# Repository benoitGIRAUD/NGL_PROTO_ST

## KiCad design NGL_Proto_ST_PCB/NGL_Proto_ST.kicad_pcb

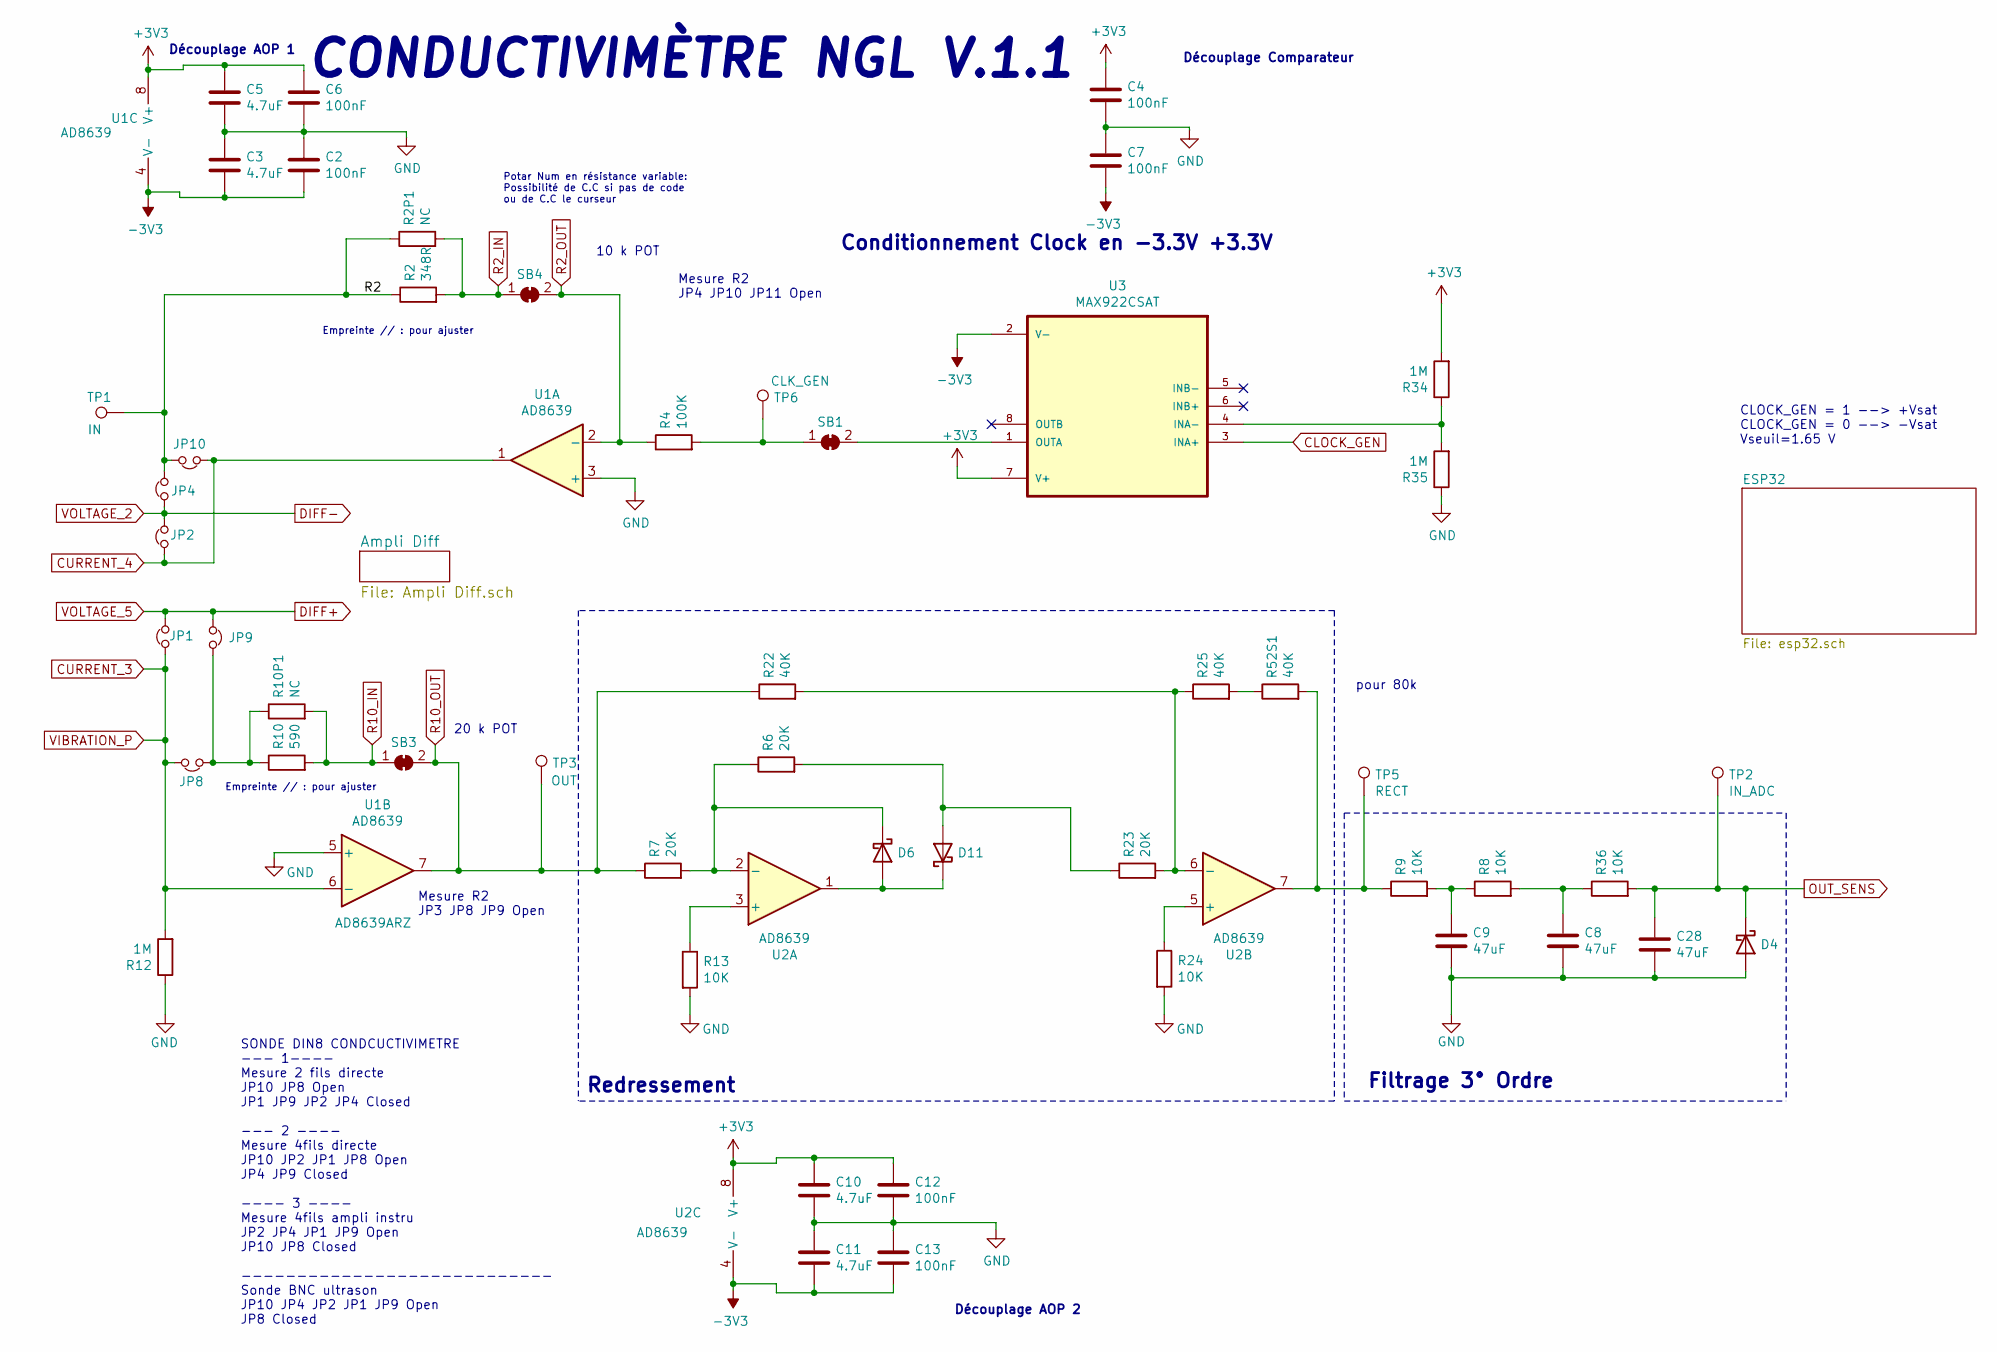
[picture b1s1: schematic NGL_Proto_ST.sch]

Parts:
C2, C4, C6, C7, C12, C13: 100nF; C_0805_2012Metric_Pad1.18x1.45mm_HandSolder
C3, C5, C10, C11: 4.7uF; C_0805_2012Metric_Pad1.18x1.45mm_HandSolder
C8, C9, C28: 47uF; C_0805_2012Metric_Pad1.18x1.45mm_HandSolder
D4, D6, D11: D_Schottky; SOT-323_SC-70_Handsoldering; MPN BAT54WFILMY
JP1, JP2, JP4, JP8, JP9, JP10: Jumper_NC_Small; PinHeader_1x02_P2.54mm_Vertical
R2: 348R; R_0805_2012Metric_Pad1.20x1.40mm_HandSolder
R2P1, R10P1: NC; R_0805_2012Metric_Pad1.20x1.40mm_HandSolder
R4: 100K; R_0805_2012Metric_Pad1.20x1.40mm_HandSolder
R6, R7, R23: 20K; R_0805_2012Metric_Pad1.20x1.40mm_HandSolder
R8, R9, R13, R24, R36: 10K; R_0805_2012Metric_Pad1.20x1.40mm_HandSolder
R10: 590; R_0805_2012Metric_Pad1.20x1.40mm_HandSolder
R12, R34, R35: 1M; R_0805_2012Metric_Pad1.20x1.40mm_HandSolder
R22, R25, R52S1: 40K; R_0805_2012Metric_Pad1.20x1.40mm_HandSolder
SB1, SB3, SB4: SB; SolderJumper-2_P1.3mm_Open_RoundedPad1.0x1.5mm
TP1: IN; PinHeader_1x01_P2.54mm_Vertical
TP2: IN_ADC; PinHeader_1x01_P2.54mm_Vertical
TP3: OUT; PinHeader_1x01_P2.54mm_Vertical
TP5: RECT; PinHeader_1x01_P2.54mm_Vertical
TP6: CLK_GEN; TestPoint_Pad_D3.0mm
U1, U2: AD8639; ADA4522-2ARZ; MPN AD8639
U3: MAX922CSAT; SOIC127P600X175-8N; MPN MAX922CSAT

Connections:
-3V3: C2.2, C3.2, C7.2, C11.2, C13.2, U1.4 (V-), U2.4 (V-), U3.2 (V-); also elsewhere on the board
/R2: JP4.2, JP10.2, R2.1, R2P1.1, TP1.1
CLOCK_GEN: U3.3 (INA+); also elsewhere on the board
CURRENT_3: JP1.1, JP8.2, R12.2, U1.6 (-); also elsewhere on the board
CURRENT_4: JP2.1, JP10.1, U1.1; also elsewhere on the board
DIFF+: JP1.2, JP9.1; also elsewhere on the board
DIFF-: JP2.2, JP4.1; also elsewhere on the board
unnamed: C8.1, R8.2, R36.1
unnamed: C9.1, R8.1, R9.2
unnamed: D6.1 (K), R6.1, R7.2, U2.2 (-)
unnamed: D6.2 (A), D11.1 (K), U2.1
unnamed: D11.2 (A), R6.2, R23.1
unnamed: JP8.1, JP9.2, R10.1, R10P1.1
unnamed: R4.2, SB1.1 (A), TP6.1
unnamed: R13.1, U2.3 (+)
unnamed: R22.2, R23.2, R25.1, U2.6 (-)
unnamed: R24.1, U2.5 (+)
unnamed: R25.2, R52S1.1
unnamed: R34.1, R35.2, U3.4 (INA-)
unnamed: R9.1, R52S1.2, TP5.1, U2.7
unnamed: SB1.2 (B), U3.1 (OUTA)
OUT_SENS: C28.1, D4.1 (K), R36.2, TP2.1; also elsewhere on the board
R2_IN: R2.2, R2P1.2, SB4.1 (A); also elsewhere on the board
R2_OUT: R4.1, SB4.2 (B), U1.2 (-); also elsewhere on the board
R10_IN: R10.2, R10P1.2, SB3.1 (A); also elsewhere on the board
R10_OUT: R7.1, R22.1, SB3.2 (B), TP3.1, U1.7; also elsewhere on the board

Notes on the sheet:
SONDE DIN8 CONDCUCTIVIMETRE --- 1---- Mesure 2 fils directe JP10 JP8 Open JP1 JP9 JP2 JP4 Closed --- 2 ---- Mesure 4fils directe JP10 JP2 JP1 JP8 Open JP4 JP9 Closed ---- 3 ---- Mesure 4fils ampli instru JP2 JP4 JP1 JP9 Open JP10 JP8 Closed ---------------------------- Sonde BNC ultrason JP10 JP4 J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
Mesure R2 JP4 JP10 JP11 Open
Mesure R2 JP3 JP8 JP9 Open
Découplage AOP 2
Découplage AOP 1
Conditionnement Clock en -3.3V +3.3V
Redressement
Filtrage 3° Ordre
Découplage Comparateur
CLOCK_GEN = 1 --> +Vsat CLOCK_GEN = 0 --> -Vsat Vseuil=1.65 V
Potar Num en résistance variable: Possibilité de C.C si pas de code ou de C.C le curseur
pour 80k
CONDUCTIVIMÈTRE NGL V.1.1
10 k POT
20 k POT
Empreinte // : pour ajuster

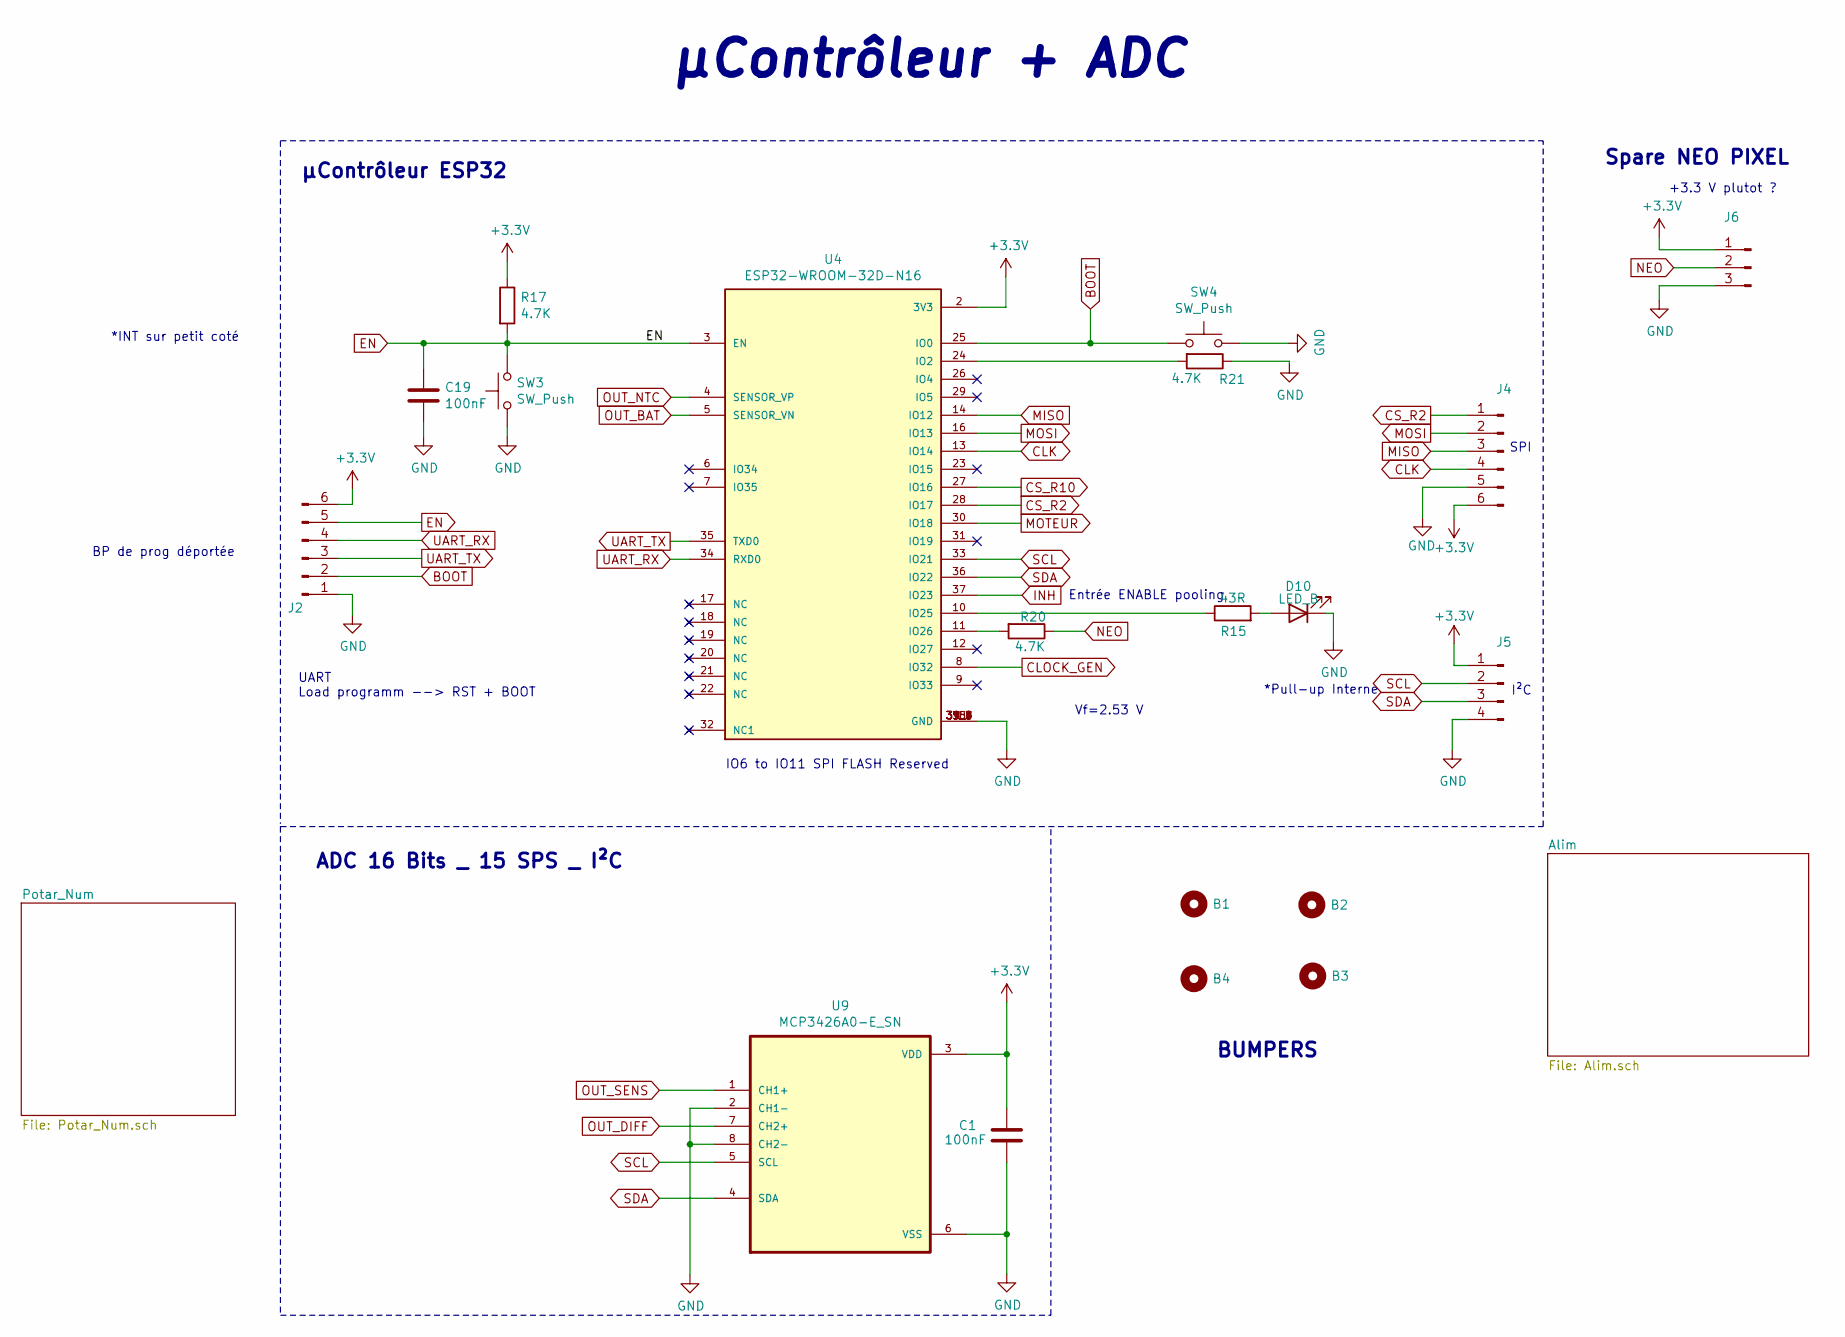
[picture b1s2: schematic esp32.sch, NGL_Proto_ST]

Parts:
B1, B2, B3, B4: BUMPER; SJ5003; MPN SJ5003
C1, C19: 100nF; C_0805_2012Metric_Pad1.18x1.45mm_HandSolder
D10: LED_B; LED_D3.0mm
J2: Conn_01x04_Male; PinHeader_1x06_P2.54mm_Vertical
J4: Conn_01x06_Male; PinHeader_1x06_P2.54mm_Vertical
J5: Conn_01x04_Male; PinHeader_1x04_P2.54mm_Vertical
J6: Conn_01x03_Male; PinHeader_1x03_P2.54mm_Vertical
R15: 43R; R_0805_2012Metric_Pad1.20x1.40mm_HandSolder
R17, R20, R21: 4.7K; R_0805_2012Metric_Pad1.20x1.40mm_HandSolder
SW3, SW4: SW_Push; 3-1825910-5; MPN 3-1825910-5
U4: ESP32-WROOM-32D-N16; MODULE_ESP32-WROOM-32D; PARTREV 1.4
U9: MCP3426A0-E_SN; SOIC127P600X175-8N; MPN MCP3426A0-E_SN

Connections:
BOOT: J2.2, SW4.1, U4.25 (IO0)
CLK: J4.4, U4.13 (IO14); also elsewhere on the board
CLOCK_GEN: U4.8 (IO32); also elsewhere on the board
CS_R10: U4.27 (IO16); also elsewhere on the board
EN: C19.1, J2.5, R17.2, SW3.2, U4.3 (EN)
INH: U4.37 (IO23); also elsewhere on the board
MISO: J4.3, U4.14 (IO12)
MOSI: J4.2, U4.16 (IO13); also elsewhere on the board
MOTEUR: U4.30 (IO18); also elsewhere on the board
NEO: J6.2, R20.1
unnamed: D10.2 (A), R15.2
unnamed: R15.1, U4.10 (IO25)
unnamed: R20.2, U4.11 (IO26)
unnamed: R21.2, U4.24 (IO2)
OUT_BAT: U4.5 (SENSOR_VN); also elsewhere on the board
OUT_DIFF: U9.7 (CH2+); also elsewhere on the board
OUT_NTC: U4.4 (SENSOR_VP); also elsewhere on the board
OUT_SENS: U9.1 (CH1+); also elsewhere on the board
SCL: J5.2, U4.33 (IO21), U9.5 (SCL)
SDA: J5.3, U4.36 (IO22), U9.4 (SDA)

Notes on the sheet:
IO6 to IO11 SPI FLASH Reserved
UART Load programm --> RST + BOOT
SPI
I²C
μContrôleur ESP32
Spare NEO PIXEL
ADC 16 Bits _ 15 SPS _ I²C
BUMPERS
+3.3 V plutot ?
Vf=2.53 V
μContrôleur + ADC
*Pull-up Interne
*INT sur petit coté
Entrée ENABLE pooling
BP de prog déportée

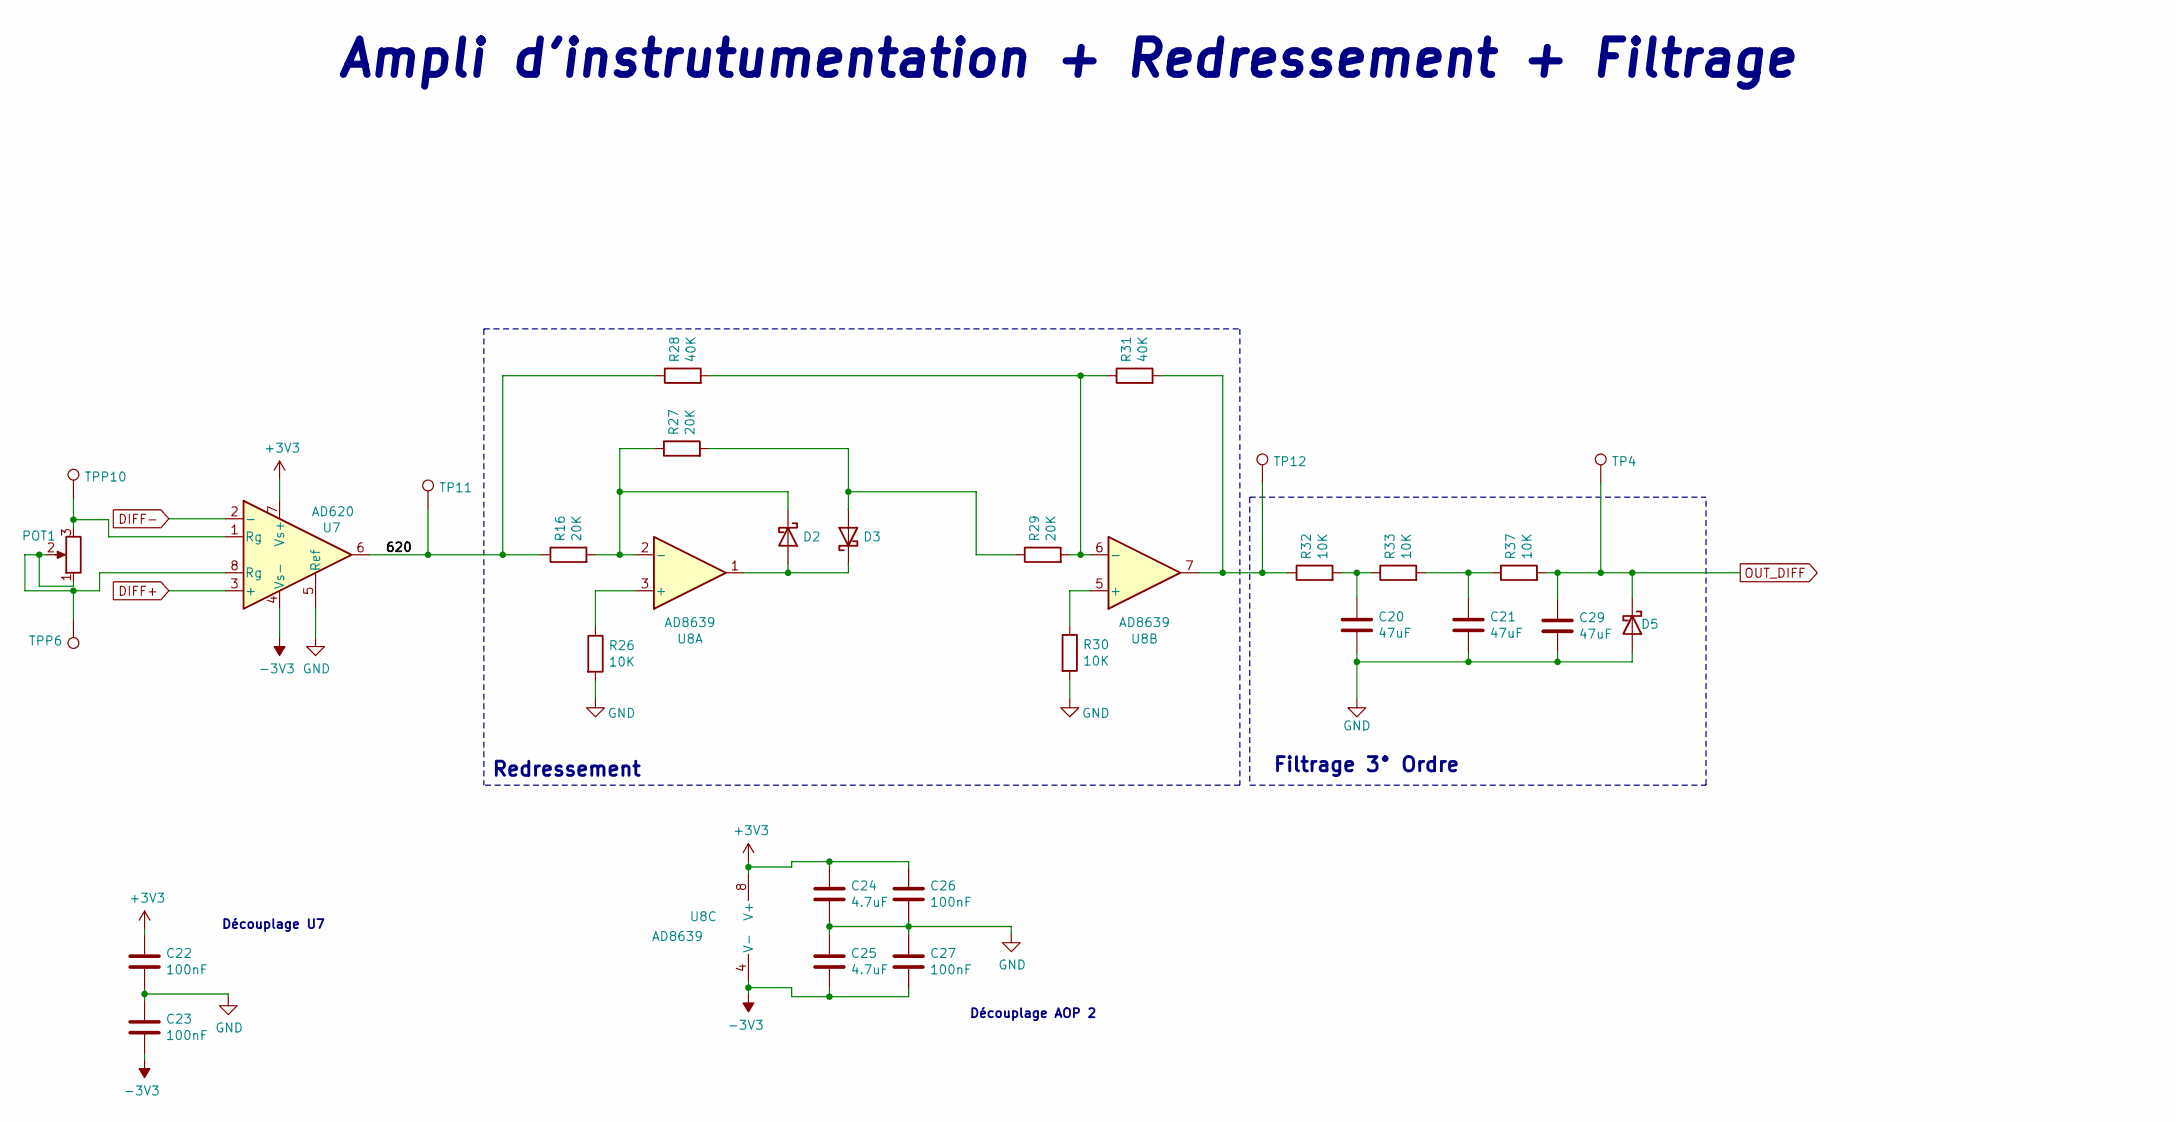
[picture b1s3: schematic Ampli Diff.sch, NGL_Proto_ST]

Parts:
C20, C21, C29: 47uF; C_0805_2012Metric_Pad1.18x1.45mm_HandSolder
C22, C23, C26, C27: 100nF; C_0805_2012Metric_Pad1.18x1.45mm_HandSolder
C24, C25: 4.7uF; C_0805_2012Metric_Pad1.18x1.45mm_HandSolder
D2, D3, D5: D_Schottky; SOT-323_SC-70_Handsoldering; MPN BAT54WFILMY
POT1: 50k; 3224X-1-502E
R16, R27, R29: 20K; R_0805_2012Metric_Pad1.20x1.40mm_HandSolder
R26, R30, R32, R33, R37: 10K; R_0805_2012Metric_Pad1.20x1.40mm_HandSolder
R28, R31: 40K; R_0805_2012Metric_Pad1.20x1.40mm_HandSolder
TP4, TP11, TP12: TestPoint; PinHeader_1x01_P2.54mm_Vertical
TPP6: TestPoint; TestPoint_Pad_D3.0mm
TPP10: TestPointPad; TestPoint_Pad_D3.0mm
U7: AD620; SOIC127P600X175-8N; MPN AD620
U8: AD8639; ADA4522-2ARZ; MPN AD8639

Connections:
-3V3: C23.2, C25.2, C27.2, U7.4 (Vs-), U8.4 (V-); also elsewhere on the board
/Ampli Diff/620: R16.1, R28.1, TP11.1, U7.6
DIFF+: U7.3 (+); also elsewhere on the board
DIFF-: U7.2 (-); also elsewhere on the board
unnamed: C20.1, R32.2, R33.1
unnamed: C21.1, R33.2, R37.1
unnamed: D2.1 (K), R16.2, R27.1, U8.2 (-)
unnamed: D2.2 (A), D3.1 (K), U8.1
unnamed: D3.2 (A), R27.2, R29.1
unnamed: POT1.1, POT1.2, TPP6.1, U7.8 (Rg)
unnamed: POT1.3, TPP10.1, U7.1 (Rg)
unnamed: R26.1, U8.3 (+)
unnamed: R28.2, R29.2, R31.1, U8.6 (-)
unnamed: R30.1, U8.5 (+)
unnamed: R31.2, R32.1, TP12.1, U8.7
OUT_DIFF: C29.1, D5.1 (K), R37.2, TP4.1; also elsewhere on the board

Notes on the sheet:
Redressement
Filtrage 3° Ordre
Ampli d'instrutumentation + Redressement + Filtrage
Découplage U7
Découplage AOP 2

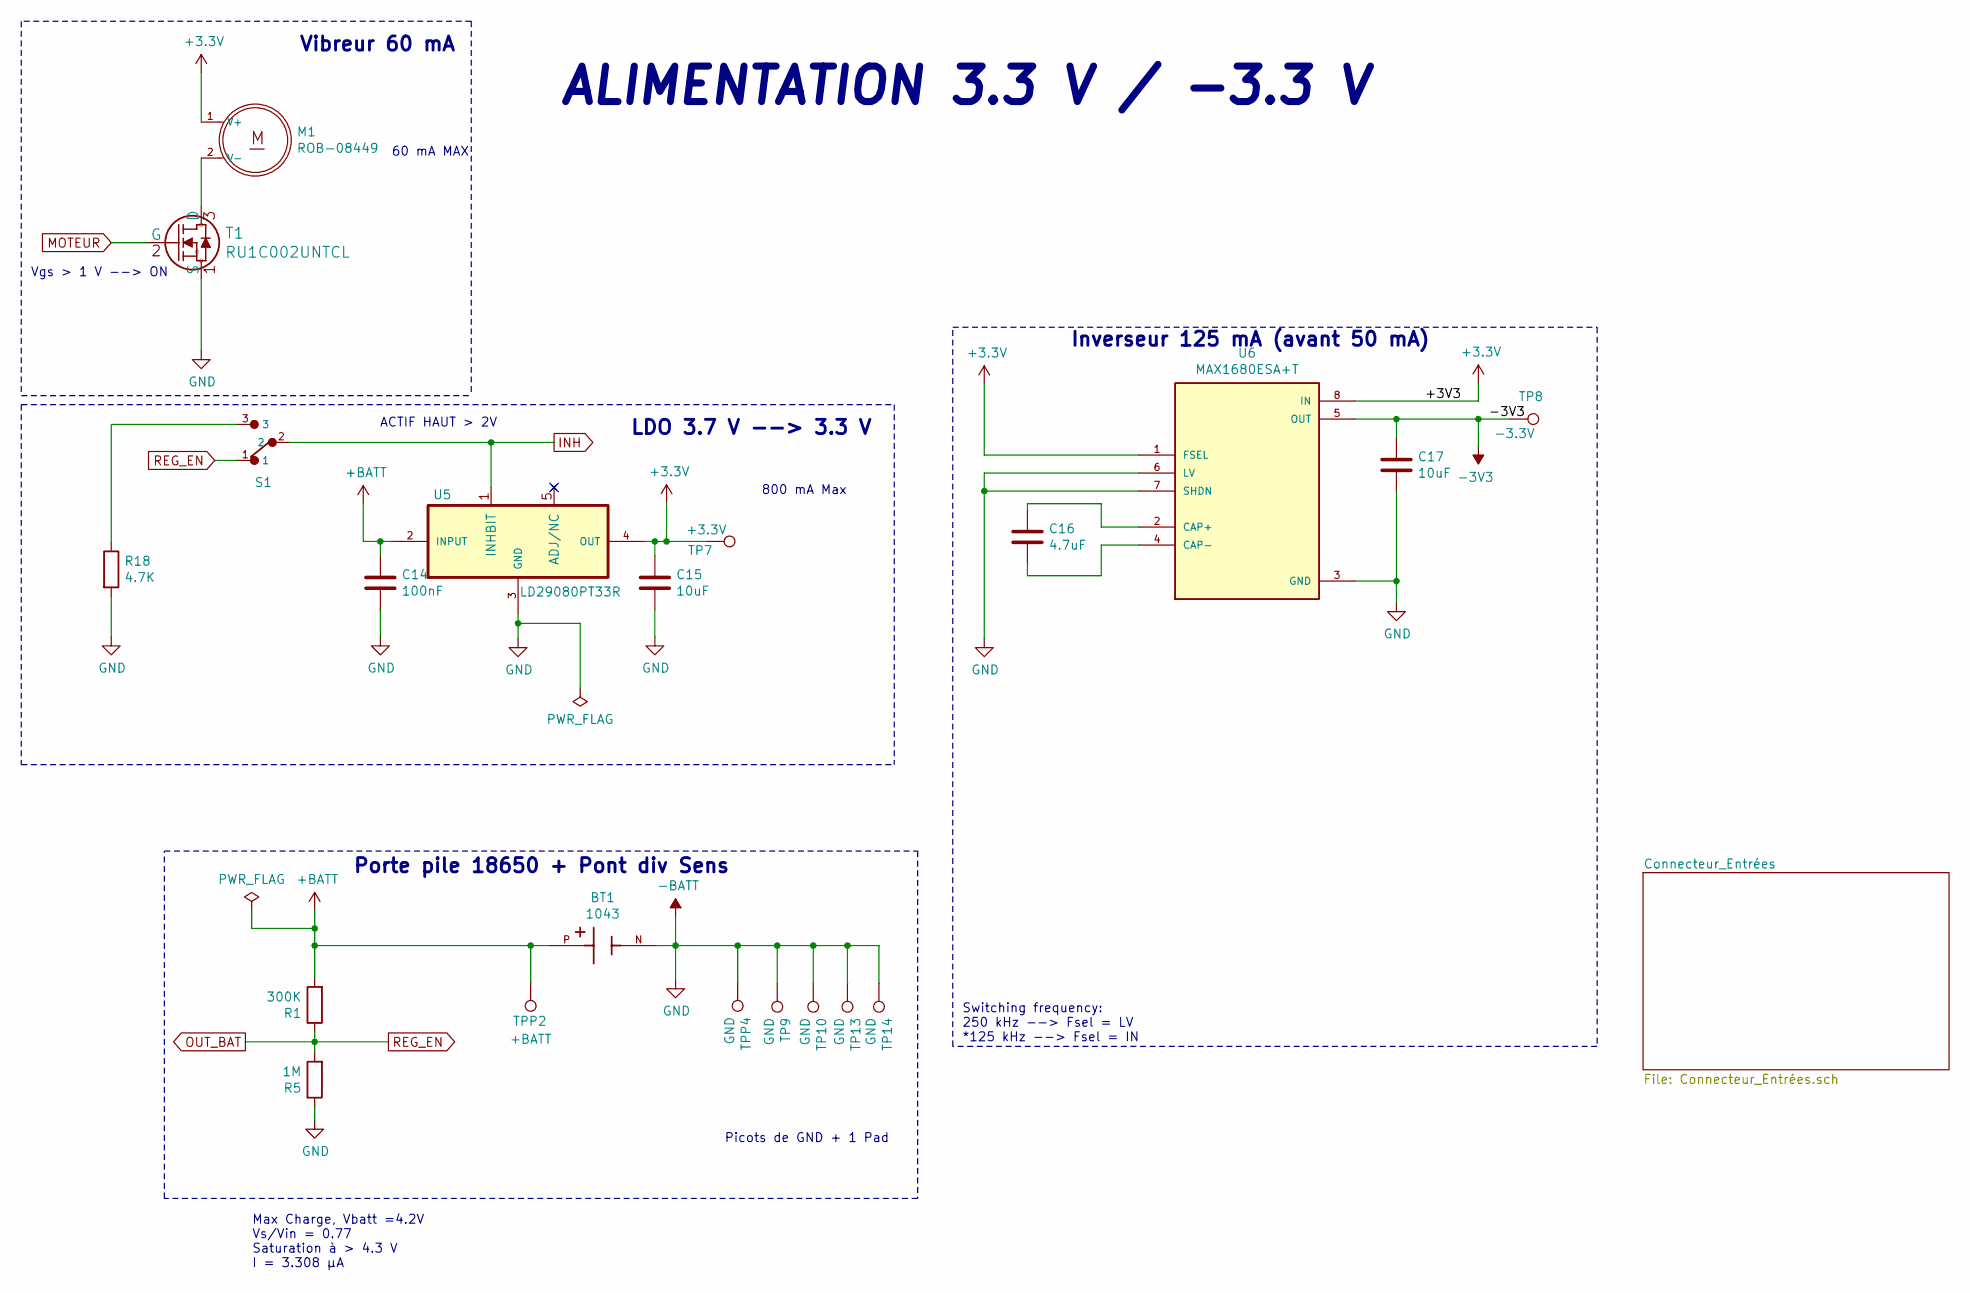
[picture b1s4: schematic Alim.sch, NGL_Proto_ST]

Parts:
BT1: 1043; BAT_1043; MPN 1043
C14: 100nF; C_0805_2012Metric_Pad1.18x1.45mm_HandSolder
C15, C17: 10uF; C_0805_2012Metric_Pad1.18x1.45mm_HandSolder
C16: 4.7uF; C_0805_2012Metric_Pad1.18x1.45mm_HandSolder
M1: ROB-08449; PinHeader_1x02_P2.54mm_Vertical
R1: 300K; R_0805_2012Metric_Pad1.20x1.40mm_HandSolder
R5: 1M; R_0805_2012Metric_Pad1.20x1.40mm_HandSolder
R18: 4.7K; R_0805_2012Metric_Pad1.20x1.40mm_HandSolder
S1: 1101M2S3CQE2; SW_1101M2S3CQE2
T1: RU1C002UNTCL
TP7: +3.3V; PinHeader_1x01_P2.54mm_Vertical
TP8: -3.3V; PinHeader_1x01_P2.54mm_Vertical
TP9, TP10, TP13, TP14: GND; PinHeader_1x01_P2.54mm_Vertical
TPP2: +BATT; TestPoint_Pad_D3.0mm
TPP4: GND; TestPoint_Pad_4.0x4.0mm
U5: LD29080PT33R; DPAK114P990X239-6N; MPN LF33CDT-TR
U6: MAX1680ESA+T; SOIC127P600X175-8N; PARTREV 0

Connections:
+BATT: BT1.P, C14.1, R1.2, TPP2.1, U5.2 (INPUT)
-3V3: C17.1, TP8.1, U6.5 (OUT); also elsewhere on the board
INH: S1.2, U5.1 (INHBIT); also elsewhere on the board
MOTEUR: T1.2 (G); also elsewhere on the board
unnamed: C16.1, U6.2 (CAP+)
unnamed: C16.2, U6.4 (CAP-)
unnamed: M1.2 (V-), T1.3 (D)
OUT_BAT: R1.1, R5.2, S1.1; also elsewhere on the board

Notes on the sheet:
LDO 3.7 V --> 3.3 V
Porte pile 18650 + Pont div Sens
Inverseur 125 mA (avant 50 mA)
Max Charge, Vbatt =4.2V Vs/Vin = 0.77 Saturation à > 4.3 V I = 3.308 μA
800 mA Max
ALIMENTATION 3.3 V / -3.3 V
60 mA MAX
Vgs > 1 V --> ON
Vibreur 60 mA
ACTIF HAUT > 2V
Switching frequency: 250 kHz --> Fsel = LV *125 kHz --> Fsel = IN
Picots de GND + 1 Pad

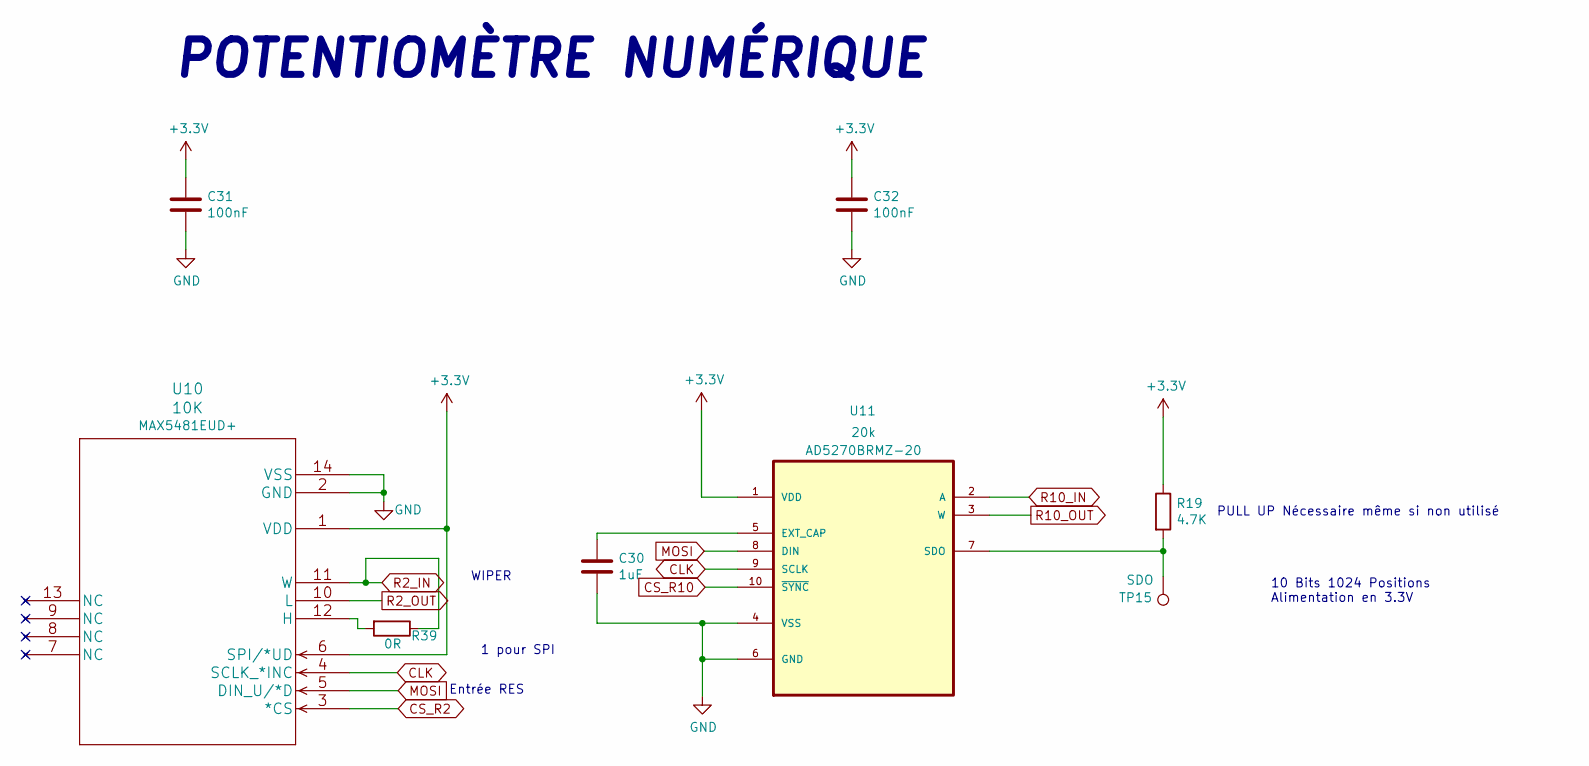
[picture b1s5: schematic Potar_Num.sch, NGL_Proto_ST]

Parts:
C30: 1uF; C_0805_2012Metric_Pad1.18x1.45mm_HandSolder
C31, C32: 100nF; C_0805_2012Metric_Pad1.18x1.45mm_HandSolder
R19: 4.7K; R_0805_2012Metric_Pad1.20x1.40mm_HandSolder
R39: 0R; R_0805_2012Metric_Pad1.20x1.40mm_HandSolder
TP15: SDO; PinHeader_1x01_P2.54mm_Vertical
U10: 10K; max5481eud&plus_T; MPN MAX5481EUD+
U11: 20k; SOP50P490X110-10N; MPN AD5270BRMZ-20

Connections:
CLK: U10.4 (SCLK_*INC), U11.9 (SCLK); also elsewhere on the board
CS_R10: U11.10 (~SYNC); also elsewhere on the board
MOSI: U10.5 (DIN_U/*D), U11.8 (DIN); also elsewhere on the board
unnamed: C30.1, U11.5 (EXT_CAP)
unnamed: R39.2, U10.12 (H)
R2_IN: R39.1, U10.11 (W); also elsewhere on the board
R2_OUT: U10.10 (L); also elsewhere on the board
R10_IN: U11.2 (A); also elsewhere on the board
R10_OUT: U11.3 (W); also elsewhere on the board

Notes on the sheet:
POTENTIOMÈTRE NUMÉRIQUE
10 Bits 1024 Positions Alimentation en 3.3V
Entrée RES
1 pour SPI
PULL UP Nécessaire même si non utilisé
WIPER

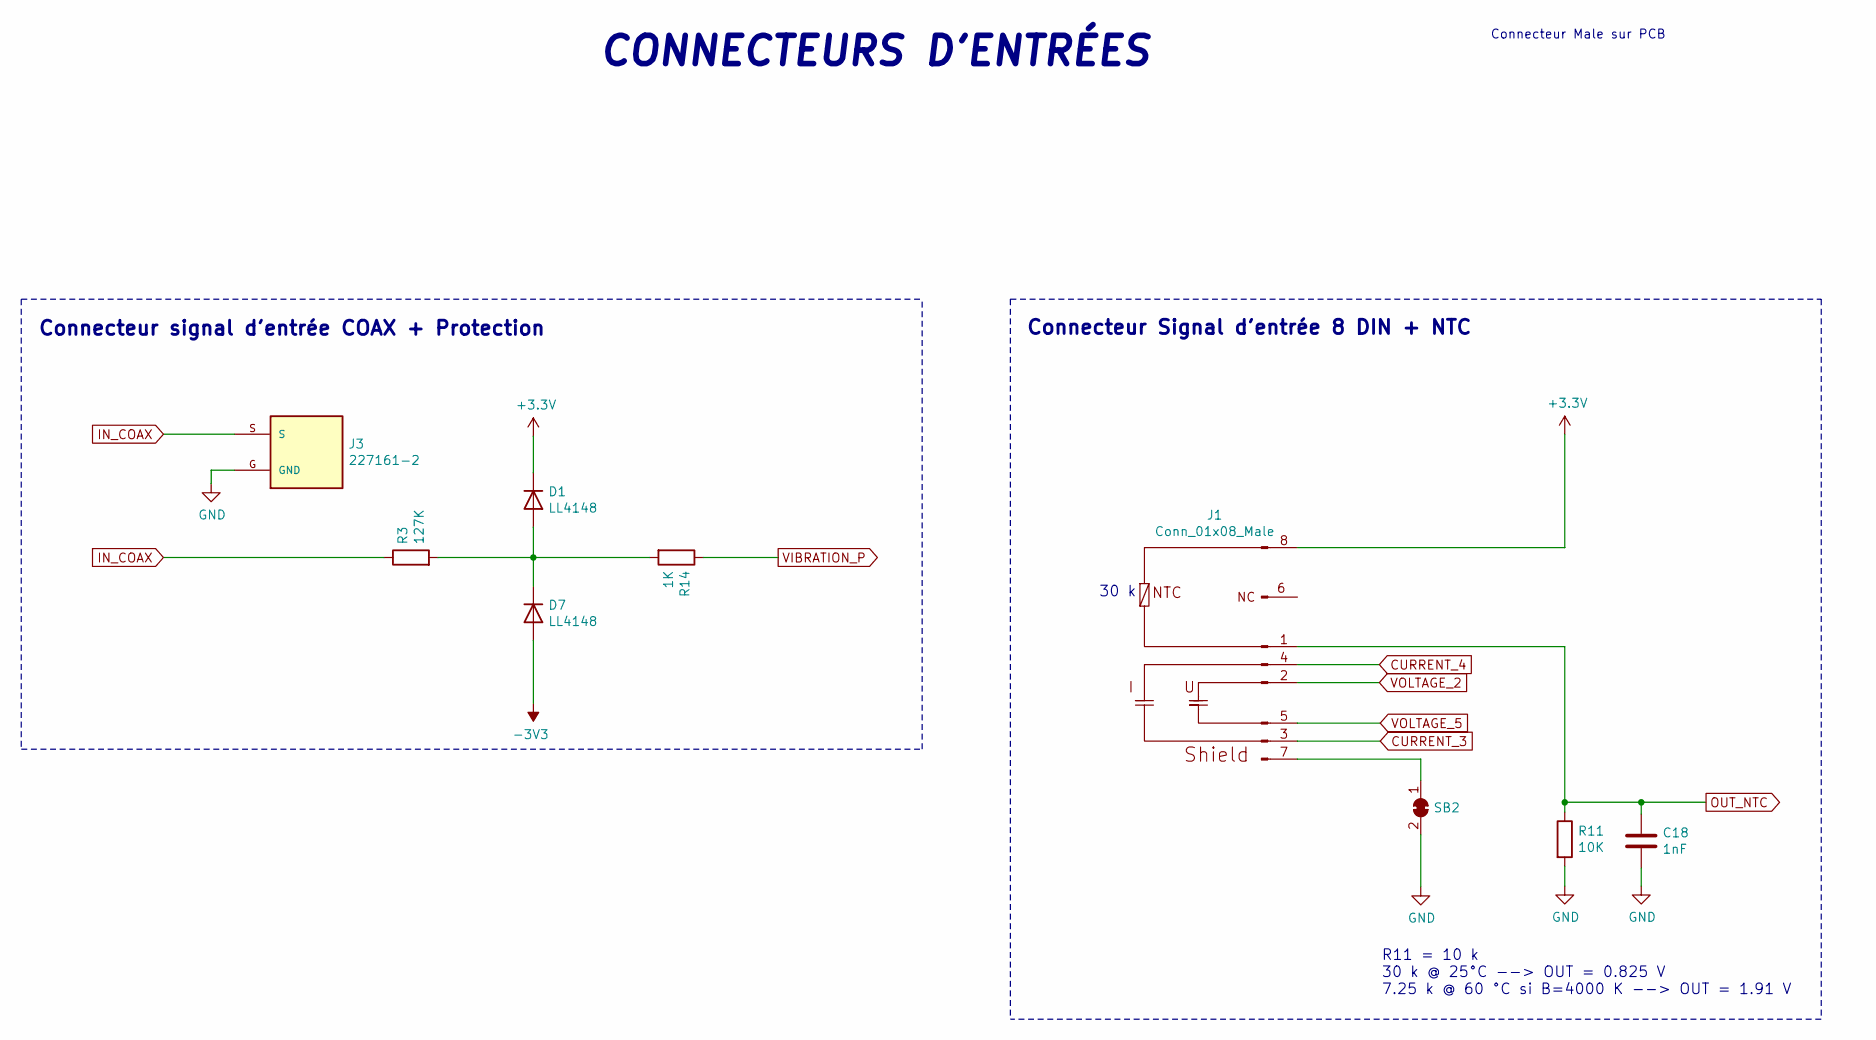
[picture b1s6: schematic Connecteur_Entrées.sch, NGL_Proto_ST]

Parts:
C18: 1nF; C_0805_2012Metric_Pad1.18x1.45mm_HandSolder
D1, D7: LL4148; D_MiniMELF; MPN LL4148
J1: Conn_01x08_Male; 8DIN_THT
J3: 227161-2; TE_5227161-2; MPN 227161-2
R3: 127K; R_0805_2012Metric_Pad1.20x1.40mm_HandSolder
R11: 10K; R_0805_2012Metric_Pad1.20x1.40mm_HandSolder
R14: 1K; R_0805_2012Metric_Pad1.20x1.40mm_HandSolder
SB2: SolderJumper_2_Bridged; SolderJumper-2_P1.3mm_Open_RoundedPad1.0x1.5mm

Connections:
-3V3: D7.2 (A); also elsewhere on the board
CURRENT_3: J1.3, R14.1; also elsewhere on the board
CURRENT_4: J1.4; also elsewhere on the board
DIFF+: J1.5; also elsewhere on the board
DIFF-: J1.2; also elsewhere on the board
IN_COAX: J3.S, R3.1
unnamed: D1.2 (A), D7.1 (K), R3.2, R14.2
unnamed: J1.7, SB2.1 (A)
OUT_NTC: C18.1, J1.1, R11.1; also elsewhere on the board

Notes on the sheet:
Connecteur Signal d'entrée 8 DIN + NTC
Connecteur signal d'entrée COAX + Protection
Connecteur Male sur PCB
30 k
R11 = 10 k 30 k @ 25°C --> OUT = 0.825 V 7.25 k @ 60 °C si B=4000 K --> OUT = 1.91 V
CONNECTEURS D'ENTRÉES

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
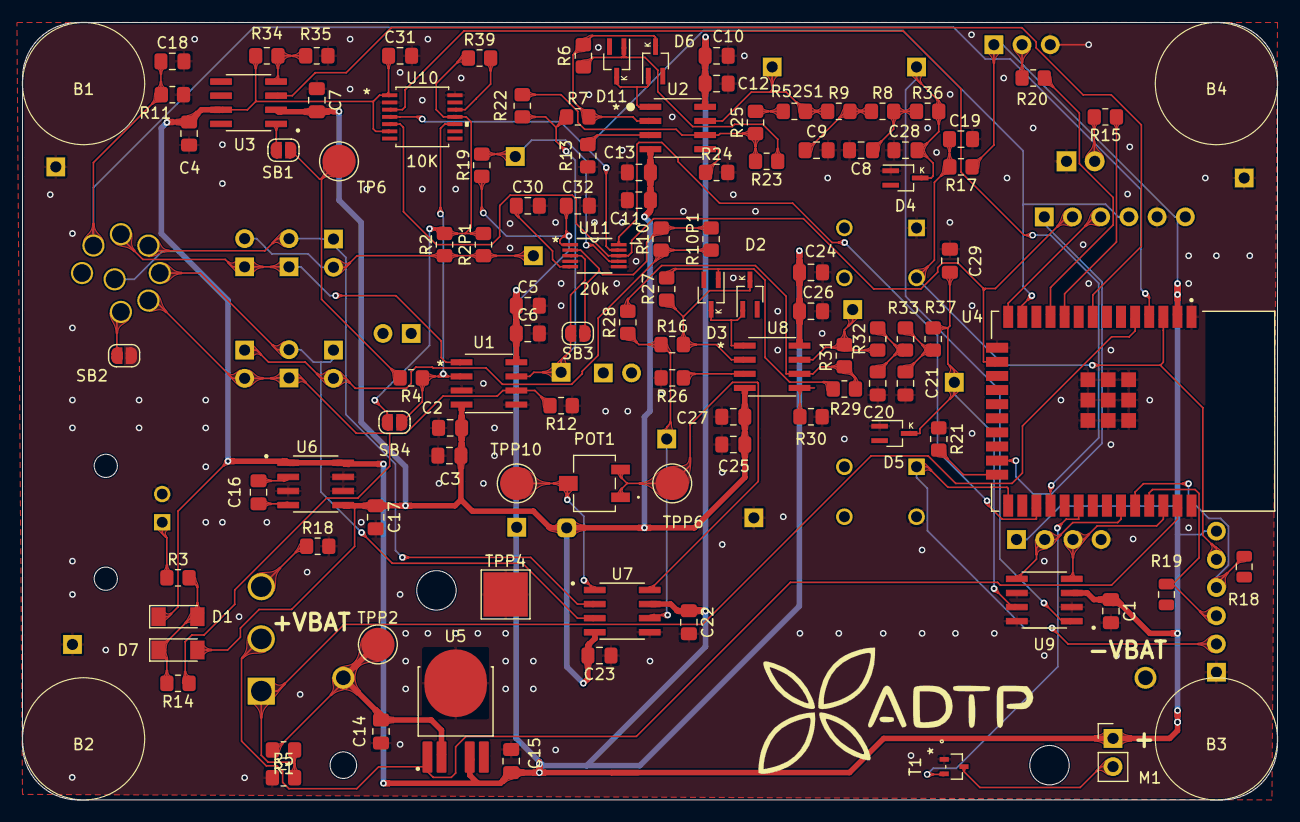
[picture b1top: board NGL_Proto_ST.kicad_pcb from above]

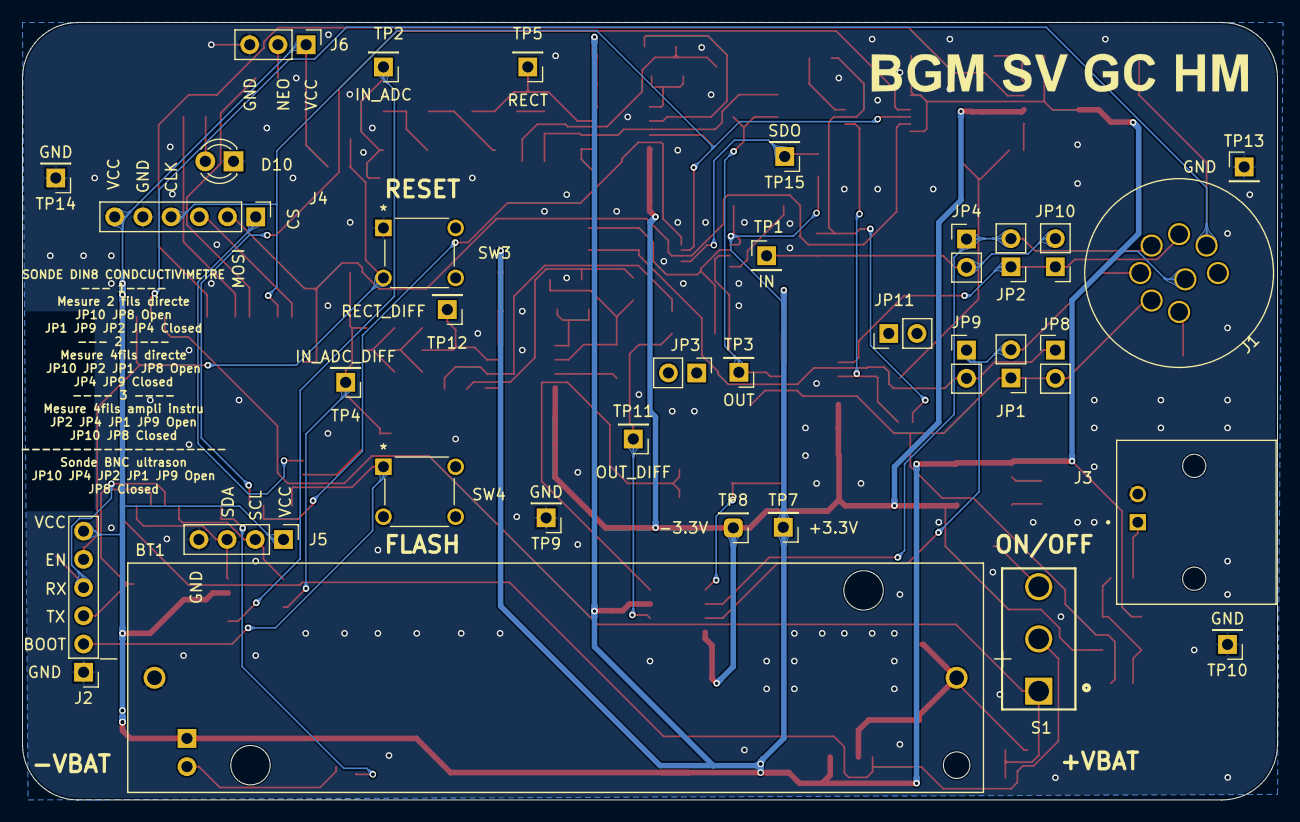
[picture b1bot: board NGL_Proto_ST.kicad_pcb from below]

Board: 2 copper layers, 113.0 x 70.0 mm, 144 parts (33 on the bottom side), 73 nets.

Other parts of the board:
G1: LOGO; logo_ADTP_Fskils
JP3, JP11: Jumper_NC_Small; PinHeader_1x02_P2.54mm_Vertical
R18#2, R19#2: 4.7K; R_0805_2012Metric_Pad1.20x1.40mm_HandSolder

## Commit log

2022-05-25 Reprise projet au propre
    Il faut ajouter les potar numérique au projet en SPI
2022-05-26 Rrecherche sur pot num et mise en page
2022-06-02 amélioration
2022-06-08 Ajuut nouveaux composants: commande 3
    Attente question ENABL E + POTAR
2022-06-08 Avancement après réunion mercredi
    finir pour mettre en review puis attente.
2022-06-09 Commit avant DSN
2022-06-09 essai pas mal
    commit avant review
2022-06-09 REVIEW !!
2022-06-09 Début ajout modifs de la review
2022-06-10 Commit avand 2° dsn
2022-06-10 avant 3° DSN
2022-06-10 tut router même masse. Attente sully pour commander
2022-06-10 Mise sur le NAS pour Sully
2022-06-10 GERBER généré: PRODUCTION
    EURO
2022-06-10 Dimensions enlevé PRODUCTION
2022-06-10 PRODUCTION après appel Philippe POUTOU
2022-06-20 BOM généré + ibom
    Check composant
2022-06-23 Placement Top ajouté

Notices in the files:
parts and their libraries:
Copyright 2021 Accelerated Designs. All rights reserved.
